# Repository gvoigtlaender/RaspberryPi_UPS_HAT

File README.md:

# RaspberryPi_UPS_HAT
## RaspberryPi UPS HAT, LIPO, Fan Control, I2C

## Project goals:
* provide backup battery (LiPo 3.7V) with I2C status interface
* small footprint to integrate into given RaspberrryPi case (LABISTS Starter Kit)
* integrated fan control (temperature based)
* onboard programmer interface (ISP)
* I2C based RPI ups service for Battery supervision, logging and shutdown (systemd, python3, smbus)

## Used items:
* Attiny 841 CPU
* LTC4054 LiPo Charger
* MT3606 Step-Up (LiPo > 5V)
* MIC5219 LDO (5V > 3.3V)
* USB Type-C connector
* resistors, capacitory (SMD 0805)

## Schematic:

## PCB:

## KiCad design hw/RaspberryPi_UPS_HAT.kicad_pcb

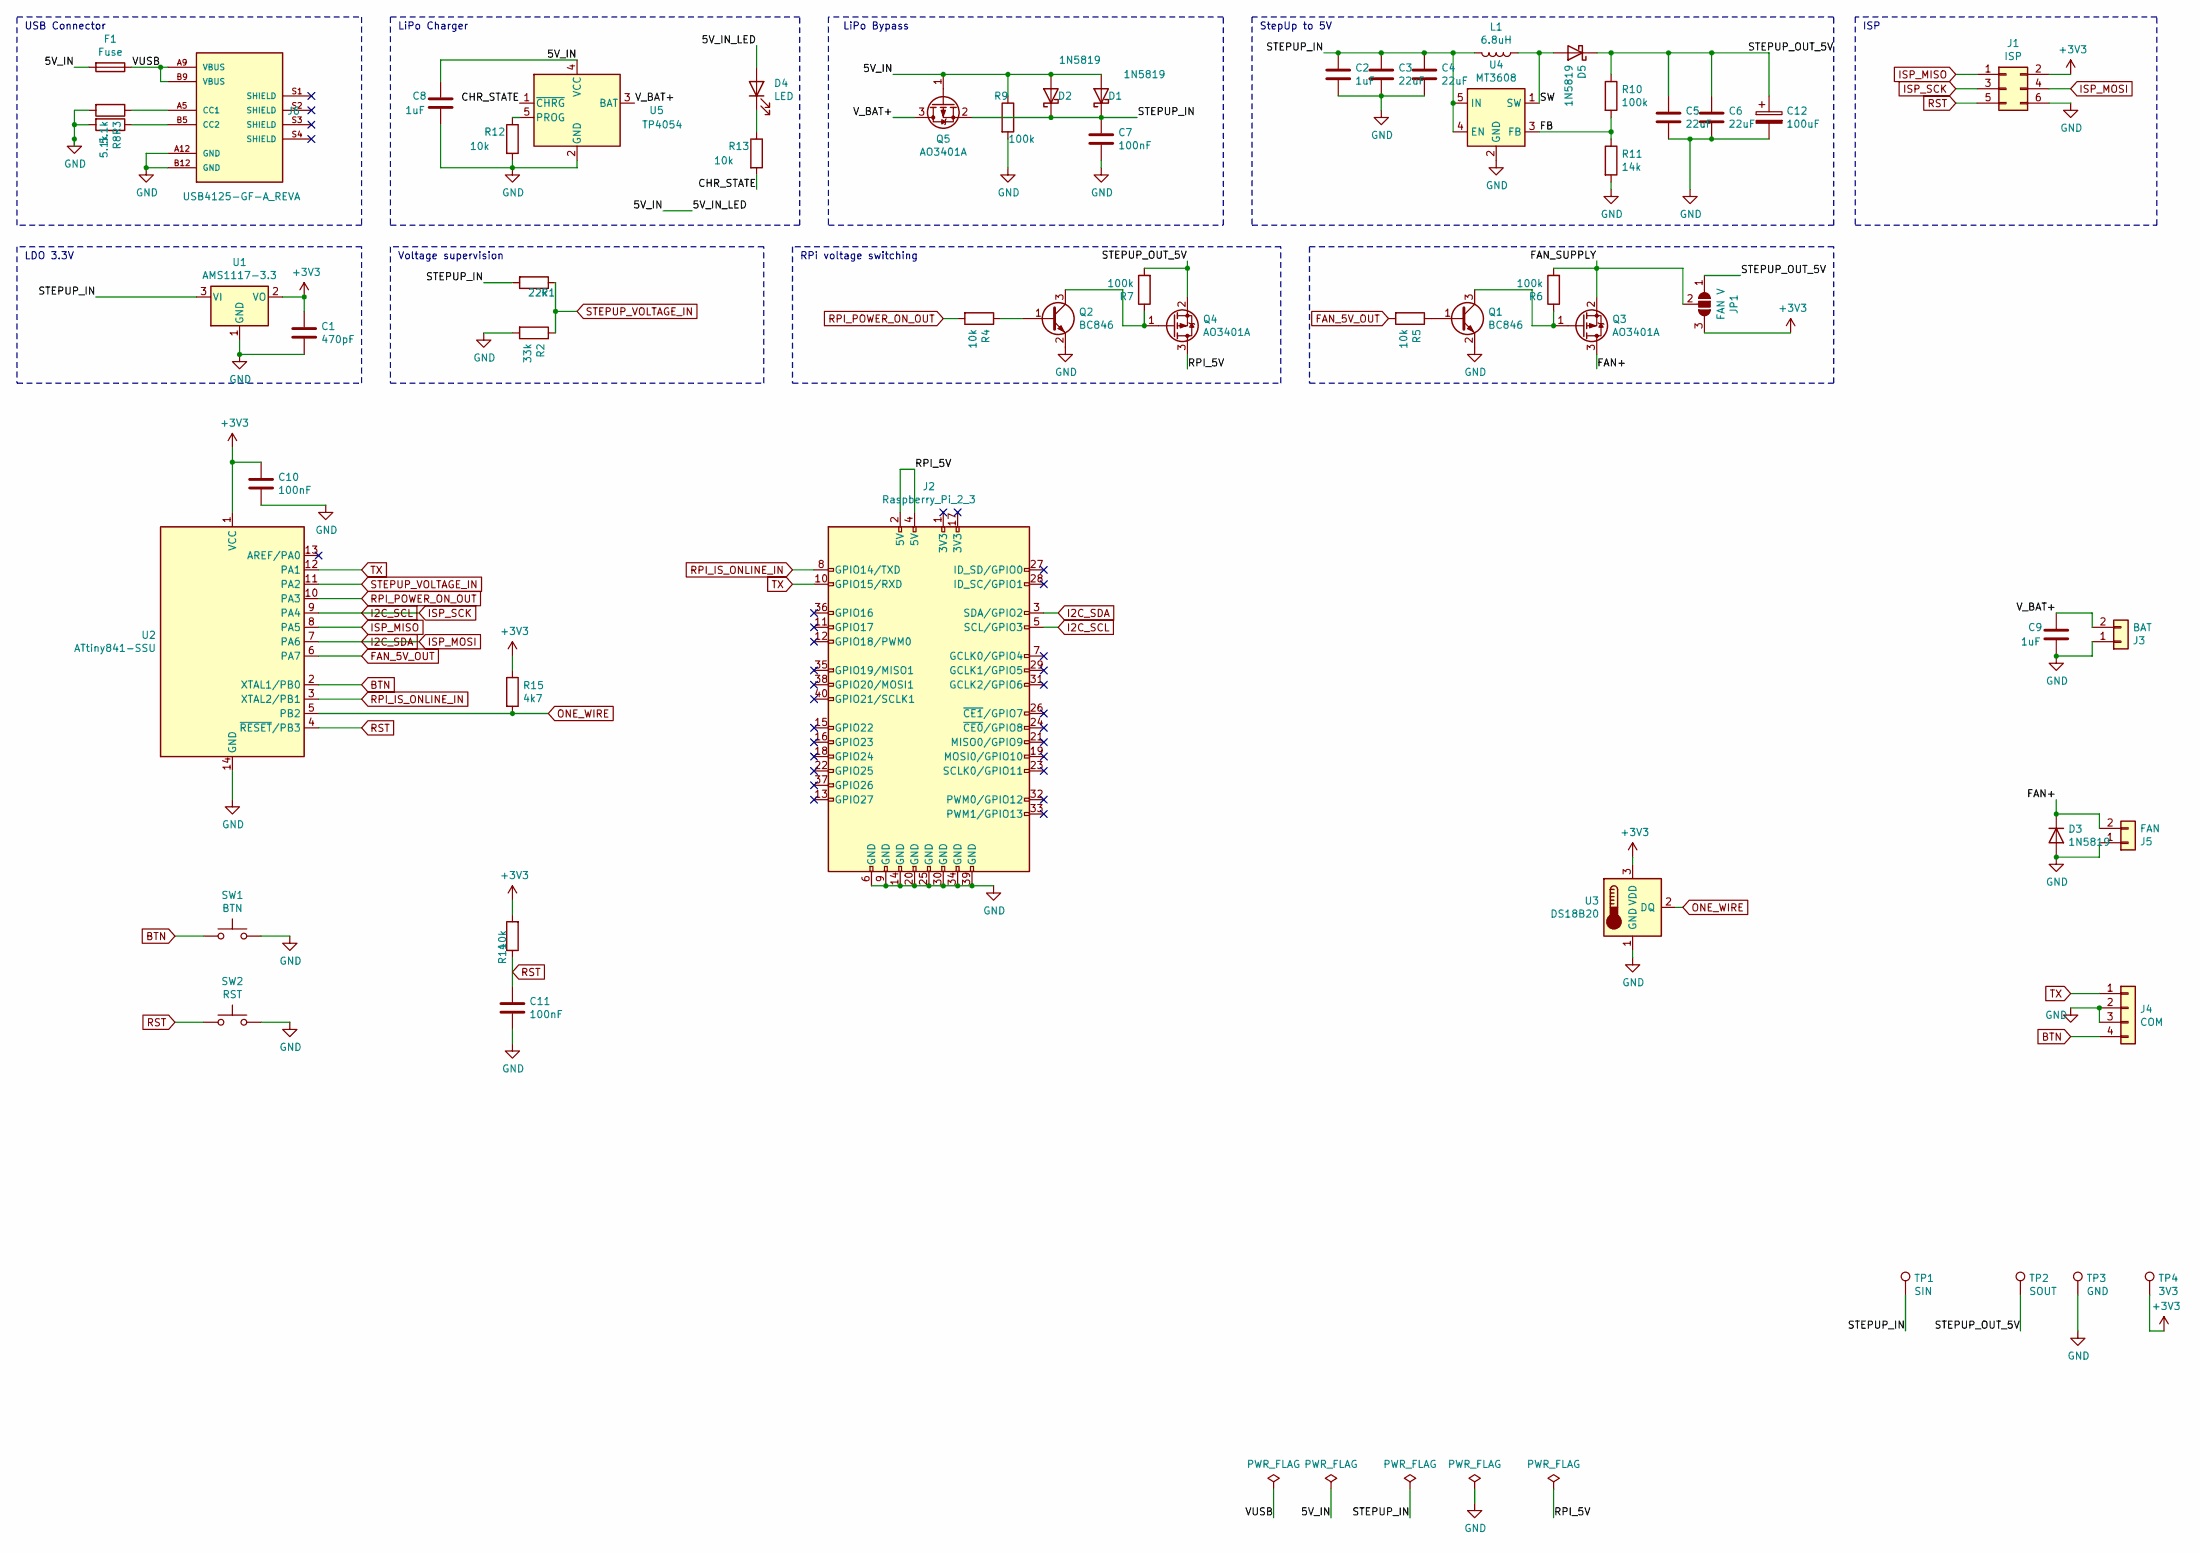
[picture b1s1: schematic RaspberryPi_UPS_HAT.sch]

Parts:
C1: 470pF; C_0805_2012Metric
C2, C8, C9: 1uF; C_0805_2012Metric
C3, C4, C5, C6: 22uF; C_0805_2012Metric
C7, C10, C11: 100nF; C_0805_2012Metric
C12: 100uF; CP_Elec_6.3x5.9
D1, D2, D3, D5: 1N5819; D_SMA
D4: LED; D_0805_2012Metric
F1: Fuse; Fuse_1812_4532Metric
J1: ISP; PinHeader_2x03_P2.54mm_Vertical
J2: Raspberry_Pi_2_3; PinSocket_2x20_P2.54mm_Vertical_RPI
J3: BAT; JST-PH-2-SMT-RA
J4: COM; PinHeader_1x04_P2.54mm_Horizontal
J5: FAN; PinHeader_1x02_P2.54mm_Horizontal
J6: USB4125-GF-A_REVA; GCT_USB4125-GF-A_REVA; PARTREV Rev A
JP1: FAN V; SolderJumper-3_P1.3mm_Open_RoundedPad1.0x1.5mm
L1: 6.8uH; L_6.3x6.3_H3
Q1, Q2: BC846; SOT-23
Q3, Q4, Q5: AO3401A; SOT-23
R1: 22k; R_0805_2012Metric
R2: 33k; R_0805_2012Metric
R3, R8: 5.1k; R_0805_2012Metric
R4, R5, R12, R13, R14: 10k; R_0805_2012Metric
R6, R7, R9, R10: 100k; R_0805_2012Metric
R11: 14k; R_0805_2012Metric
R15: 4k7; R_0805_2012Metric
SW1: BTN; SW_SPST_SKQG_WithoutStem
SW2: RST; SW_SPST_SKQG_WithoutStem
TP1: SIN; TestPoint_THTPad_D1.0mm_Drill0.5mm
TP2: SOUT; TestPoint_THTPad_D1.0mm_Drill0.5mm
TP3: GND; TestPoint_THTPad_D1.0mm_Drill0.5mm
TP4: 3V3; TestPoint_THTPad_D1.0mm_Drill0.5mm
U1: AMS1117-3.3; SOT-223-3_TabPin2
U2: ATtiny841-SSU; SOIC-14_3.9x8.7mm_P1.27mm
U3: DS18B20; TO-92_Inline
U4: MT3608; SOT-23-6_Handsoldering
U5: TP4054; SOT-23-5

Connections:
+3V3: C1.1, C10.1, J1.2, JP1.3 (B), R14.2, R15.1, TP4.1, U1.2 (VO), U2.1 (VCC), U3.3 (VDD)
/5V_IN: C8.1, D1.2 (A), D2.2 (A), D4.2 (A), F1.2, Q5.1 (G), R9.1, U5.4 (VCC)
/CHR_STATE: R13.2, U5.1 (~CHRG)
/FAN+: D3.1 (K), J5.2, Q3.3 (D)
/FAN_SUPPLY: JP1.2 (C), Q3.2 (S), R6.2
/FB: R10.2, R11.1, U4.3 (FB)
/RPI_5V: J2.2 (5V), J2.4 (5V), Q4.3 (D)
/STEPUP_IN: C2.1, C3.1, C4.1, C7.1, D1.1 (K), D2.1 (K), L1.2, Q5.2 (S), R1.2, TP1.1, U1.3 (VI), U4.4 (EN), U4.5 (IN)
/STEPUP_OUT_5V: C5.1, C6.1, C12.1, D5.1 (K), JP1.1 (A), Q4.2 (S), R7.2, R10.1, TP2.1
/SW: D5.2 (A), L1.1, U4.1 (SW)
/VUSB: F1.1, J6.A9 (VBUS), J6.B9 (VBUS)
/V_BAT+: C9.1, J3.2, Q5.3 (D), U5.3 (BAT)
BTN: J4.4, SW1.1, U2.2 (XTAL1/PB0)
FAN_5V_OUT: R5.2, U2.6 (PA7)
GND: C1.2, C2.2, C3.2, C4.2, C5.2, C6.2, C7.2, C8.2, C9.2, C10.2, C11.2, C12.2, D3.2 (A), J1.6, J2.6 (GND), J2.9 (GND), J2.14 (GND), J2.20 (GND), J2.25 (GND), J2.30 (GND), J2.34 (GND), J2.39 (GND), J3.1, J4.2, J4.3, J5.1, J6.A12 (GND), J6.B12 (GND), Q1.2 (E), Q2.2 (E), R2.2, R3.2, R8.2, R9.2, R11.2, R12.2, SW1.2, SW2.2, TP3.1, U1.1 (GND), U2.14 (GND), U3.1 (GND), U4.2 (GND), U5.2 (GND)
I2C_SCL: J1.3, J2.5 (SCL/GPIO3), U2.9 (PA4)
I2C_SDA: J1.4, J2.3 (SDA/GPIO2), U2.7 (PA6)
ISP_MISO: J1.1, U2.8 (PA5)
unnamed: D4.1 (K), R13.1
unnamed: J6.A5 (CC1), R3.1
unnamed: J6.B5 (CC2), R8.1
unnamed: Q1.1 (B), R5.1
unnamed: Q1.3 (C), Q3.1 (G), R6.1
unnamed: Q2.1 (B), R4.1
unnamed: Q2.3 (C), Q4.1 (G), R7.1
unnamed: R12.1, U5.5 (PROG)
ONE_WIRE: R15.2, U2.5 (PB2), U3.2 (DQ)
RPI_IS_ONLINE_IN: J2.8 (GPIO14/TXD), U2.3 (XTAL2/PB1)
RPI_POWER_ON_OUT: R4.2, U2.10 (PA3)
RST: C11.1, J1.5, R14.1, SW2.1, U2.4 (~RESET~/PB3)
STEPUP_VOLTAGE_IN: R1.1, R2.1, U2.11 (PA2)
TX: J2.10 (GPIO15/RXD), J4.1, U2.12 (PA1)

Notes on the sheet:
USB Connector
LiPo Charger
StepUp to 5V
LiPo Bypass
LDO 3.3V
Voltage supervision
RPi voltage switching
ISP

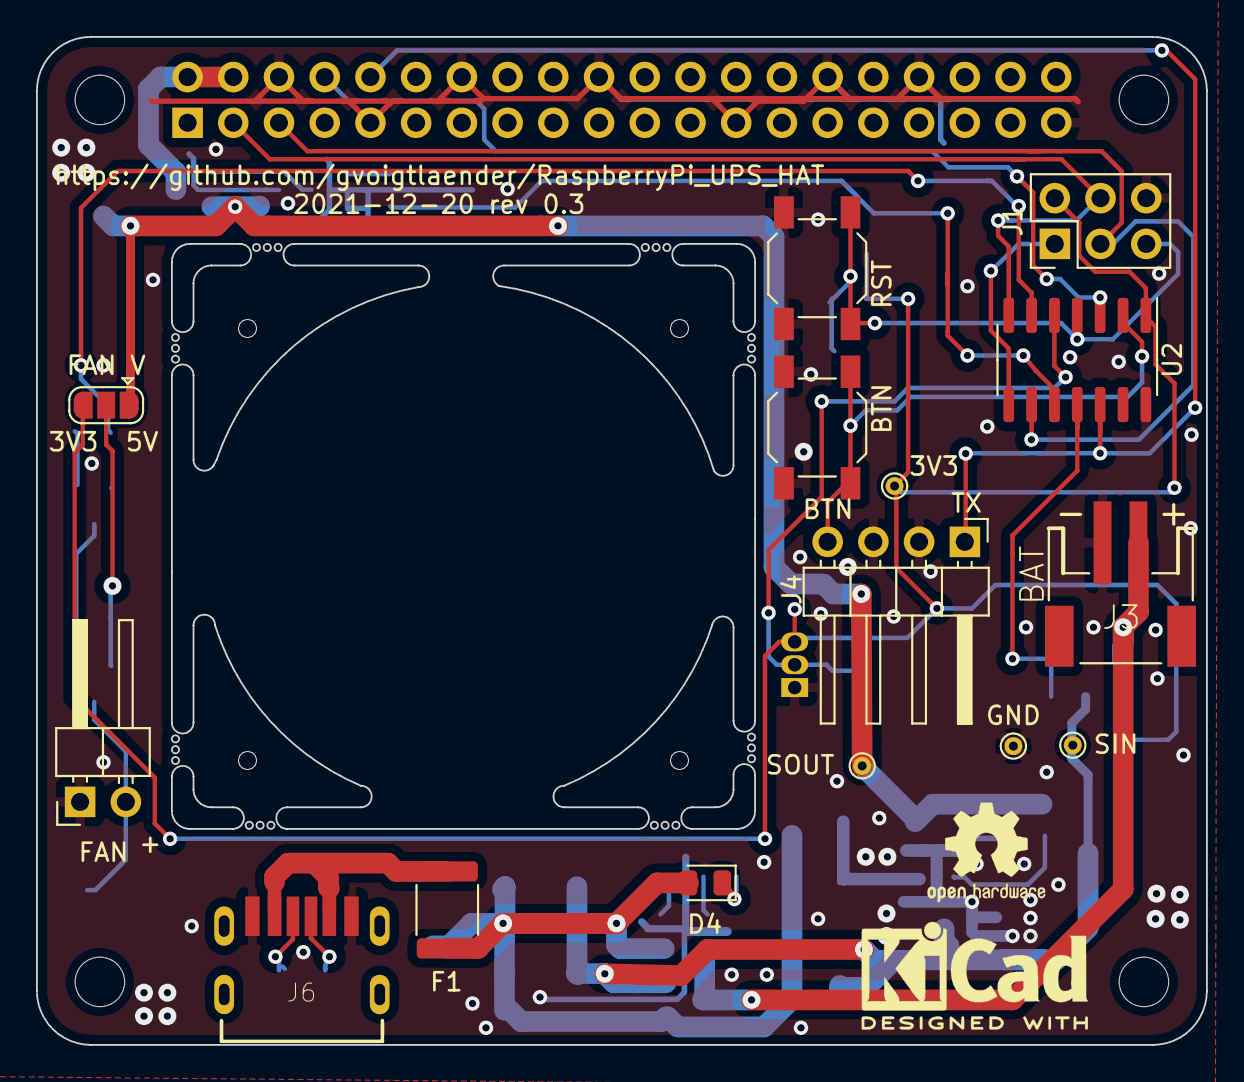
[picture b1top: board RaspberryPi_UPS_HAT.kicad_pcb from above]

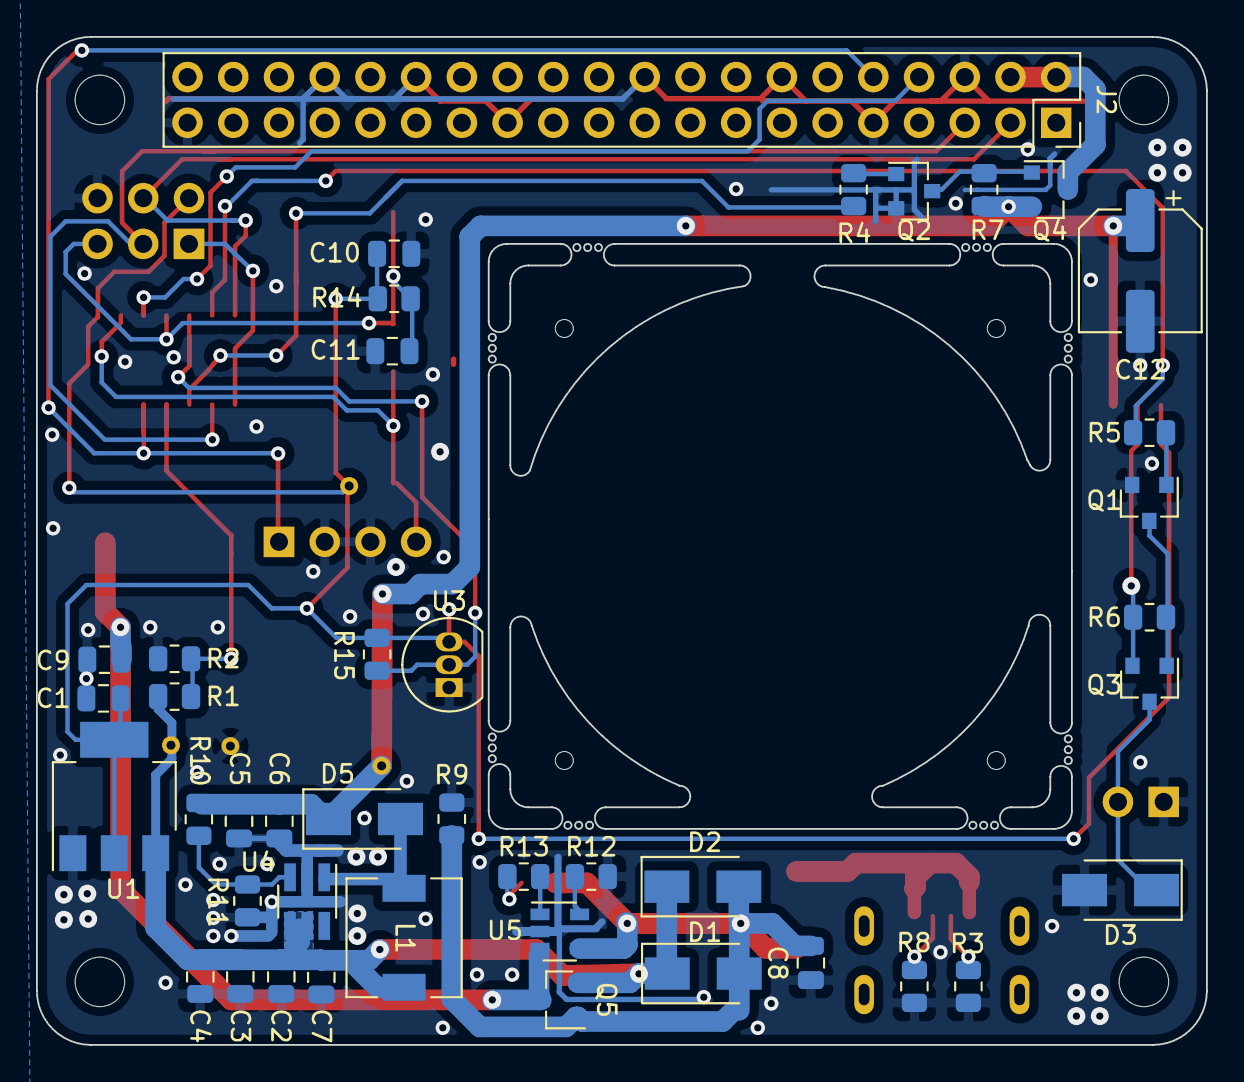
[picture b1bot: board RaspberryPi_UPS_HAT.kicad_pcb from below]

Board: 2 copper layers, 65.0 x 56.0 mm, 57 parts (42 on the bottom side), 32 nets.

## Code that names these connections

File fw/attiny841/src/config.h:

#if !defined _CONFIG_H_
#define _CONFIG_H_

#define USE_I2C
#define USE_DS18B20_AVR
#define HW_REV 1

#if HW_REV == 1
#define STEPUP_VOLTAGE_IN PIN_A2
#define RPI_POWER_ON_OUT PIN_PA3
#define FAN_5V_OUT PIN_PA7
#define BTN PIN_PB0
#define RPI_IS_ONLINE_IN PIN_PB1
#define ONE_WIRE PIN_PB2
#elif HW_REV == 2
#define RPI_POWER_ON_OUT PIN_PA2
#define FAN_5V_OUT PIN_PA3
#define ONE_WIRE PIN_PA7
#define BTN PIN_PB0
#define RPI_IS_ONLINE_IN PIN_PB1
#define STEPUP_VOLTAGE_IN PIN_PB2
#endif

#endif // _CONFIG_H_

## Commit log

2021-11-29 add code
2021-11-29 ignore cppcheck.xml output
2021-12-03 update: move defines to config.h update: im/export thr TempLow/-High via I2C
2021-12-10 bugfix: typing error
2021-12-10 update: logs, install python3-smbus
2021-12-10 bugfixes
2021-12-10 update: change directory
2021-12-11 update: readme
2021-12-12 add BOM & gerber files
2021-12-17 update: make BTN available as optional pin header
2021-12-17 update pictures
2021-12-20 update: rev0.3 - new alignmant, LCSC listed elements
2021-12-20 update: graphics for rev 0.3
